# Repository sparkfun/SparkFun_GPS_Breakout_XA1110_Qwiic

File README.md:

SparkFun GPS Breakout - XA1110
========================================

[*SparkFun GPS Breakout - XA1110 (Qwiic) (SEN-14414)*](https://www.sparkfun.com/products/14414)

The Qwiic GPS uses the Titan X1 GPS module with special I2C firmware. This library talks to the GPS module over I2C.

Repository Contents
-------------------

* **/Hardware** - Eagle design files (.brd, .sch)
* **/Libraries** - Libraries for use with the SparkFun GPS Breakout
* **/Production** - Production panel files (.brd)

Documentation
--------------
* **[SparkFun I2C GPS Library](https://github.com/sparkfun/SparkFun_I2C_GPS_Arduino_Library)** - C library for the XA1110.
* **[TinyGPS library by MikalHart](https://github.com/mikalhart/TinyGPS)** - C library for the XA1110.
* **[Hookup Guide](https://learn.sparkfun.com/tutorials/sparkfun-gps-breakout---xa1110-qwiic-hookup-guide)** - Basic hookup guide for the XA1110 GPS.
* **[SparkFun Fritzing repo](https://github.com/sparkfun/Fritzing_Parts)** - Fritzing diagrams for SparkFun products.
* **[SparkFun 3D Model repo](https://github.com/sparkfun/3D_Models)** - 3D models of SparkFun products. 
* **[SparkFun Graphical Datasheets](https://github.com/sparkfun/Graphical_Datasheets)** -Graphical Datasheets for various SparkFun products.

Product Versions
----------------
* [SEN-14414](https://www.sparkfun.com/products/14414)- The Qwiic GPS uses the Titan X1 GPS module with special I2C firmware. This library talks to the GPS module over I2C.

Version History
---------------
* [v1.0.0](https://github.com/sparkfun/SparkFun_GPS_Breakout_XA1110_Qwiic/releases/tag/V_1.0.0) - Initial Release

License Information
-------------------

This product is _**open source**_! 

Please review the LICENSE.md file for license information. 

If you have any questions or concerns on licensing, please contact techsupport@sparkfun.com.

Distributed as-is; no warranty is given.

- Your friends at SparkFun.

_<COLLABORATION CREDIT>_

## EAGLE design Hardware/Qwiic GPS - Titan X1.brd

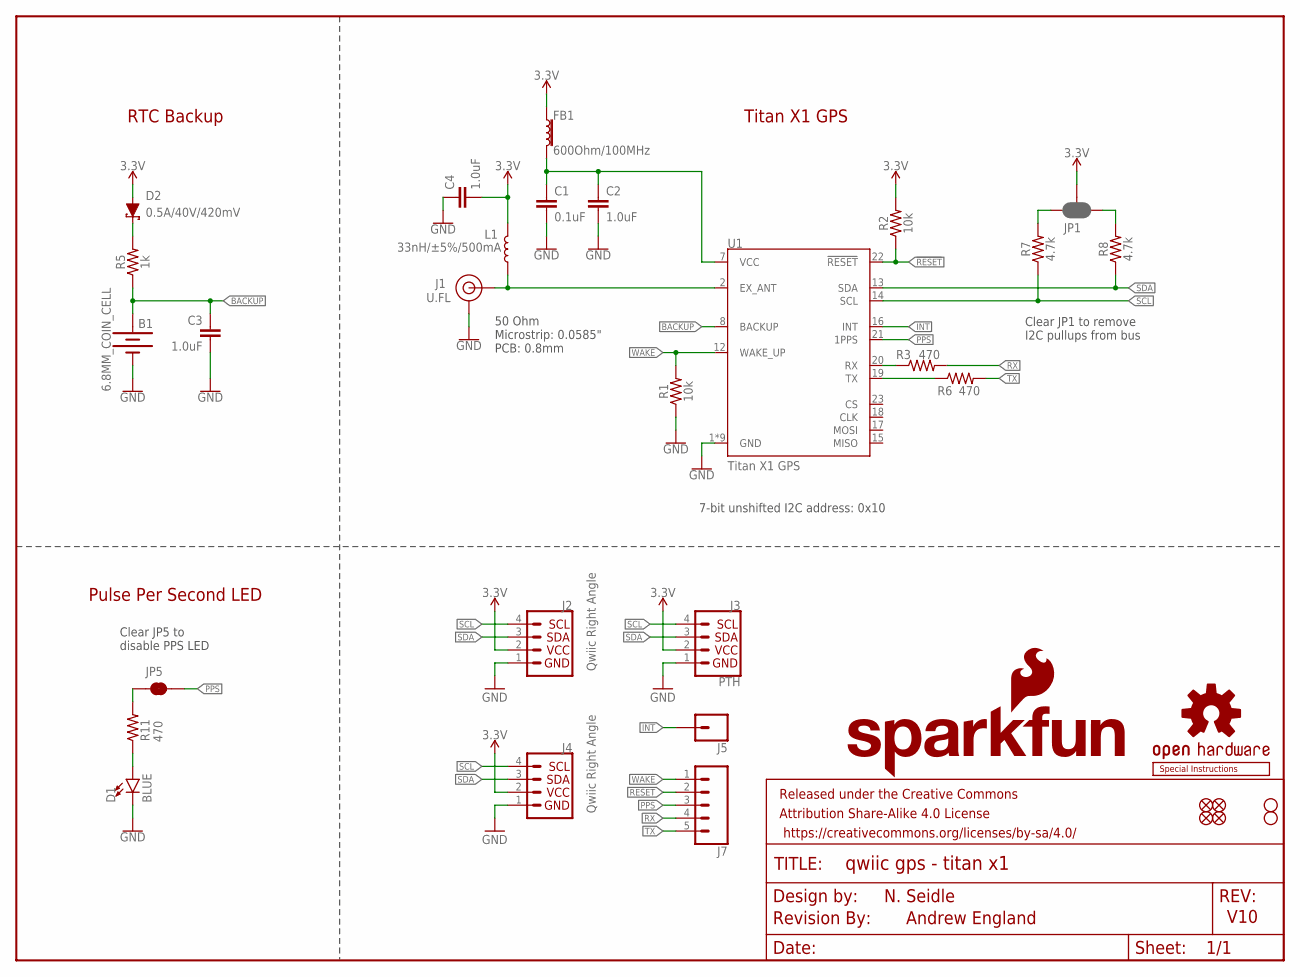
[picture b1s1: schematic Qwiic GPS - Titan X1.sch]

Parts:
B1: 6.8MM_COIN_CELL; BATTCON-6.8MM
C1: 0.1uF; 0603
C2, C3, C4: 1.0uF; 0603
D1: BLUE; LED-0603
D2: 0.5A/40V/420mV; SOD-323
FB1: 600Ohm/100MHz; 0603
FRAME1: FRAME-LETTER; CREATIVE_COMMONS
J1: U.FL
J2, J4: Qwiic Right Angle; 1X04_1MM_RA
J3: PTH; 1X04_NO_SILK
J5: CONN_01PTH_NO_SILK_YES_STOP; 1X01_NO_SILK
J7: CONN_05NO_SILK; 1X05_NO_SILK
JP1: JUMPER-SMT_3_2-NC_PASTE_SILK; SMT-JUMPER_3_2-NC_PASTE_SILK
JP2, JP6, JP7, JP8: FIDUCIALUFIDUCIAL; MICRO-FIDUCIAL
JP3, JP4: STAND-OFF
JP5: JUMPER-SMT_2_NC_TRACE_NO-SILK; SMT-JUMPER_2_NC_TRACE_NO-SILK
L1: 33nH/±5%/500mA; 0603
LOGO1: OSHW-LOGOMINI; OSHW-LOGO-MINI
LOGO2: SFE_LOGO_NAME_FLAME.1_INCH; SFE_LOGO_NAME_FLAME_.1
LOGO3: REVISION
R1, R2: 10k; 0603
R3, R6, R11: 470; 0603
R5: 1k; 0603
R7, R8: 4.7k; 0603
U1: Titan X1 GPS; TITAN_X1_GPS
U$3: SPECIAL_INSTRUCTIONS-PRODUCTION; PRODUCTION_INSTRUCTIONS

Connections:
3.3V: C4.2, D2.A, FB1.1, J2.2, J3.2 (VCC), J4.2, JP1.2, L1.2, R2.2
!RESET: J7.2, R2.1, U1.22 (!RESET)
BACKUP: B1.+, C3.1, R5.1, U1.8 (BACKUP)
EXT_ANT: J1.FEED (SIGNAL), L1.1, U1.2 (EX_ANT)
GND: B1.-, C1.2, C2.2, C3.2, C4.1, D1.C, J1.1 (GND), J1.2 (GND), J2.1, J3.1 (GND), J4.1, R1.1, U1.1 (GND), U1.3 (GND), U1.4 (GND), U1.5 (GND), U1.6 (GND), U1.9 (GND), U1.10 (GND), U1.11 (GND), U1.24 (GND)
INT: J5.1, U1.16 (INT)
unnamed: D1.A, R11.1
unnamed: JP5.1, R11.2
unnamed: JP1.1, R8.2
unnamed: D2.C, R5.2
unnamed: JP1.3, R7.2
PPS: J7.3, JP5.2, U1.21 (1PPS)
RX: J7.4, R3.2
RXLV: R3.1, U1.20 (RX)
SCL: J2.4, J3.4 (SCL), J4.4, R7.1, U1.14 (SCL)
SDA: J2.3, J3.3 (SDA), J4.3, R8.1, U1.13 (SDA)
TX: J7.5, R6.2
TXLV: R6.1, U1.19 (TX)
VCC_FILTERED: C1.1, C2.1, FB1.2, U1.7 (VCC)
WAKE: J7.1, R1.2, U1.12 (WAKE_UP)

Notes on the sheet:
N. Seidle
V10
7-bit unshifted I2C address: 0x10
Titan X1 GPS
RTC Backup
Pulse Per Second LED
50 Ohm Microstrip: 0.0585" PCB: 0.8mm
Andrew England
Clear JP1 to remove I2C pullups from bus
Clear JP5 to disable PPS LED

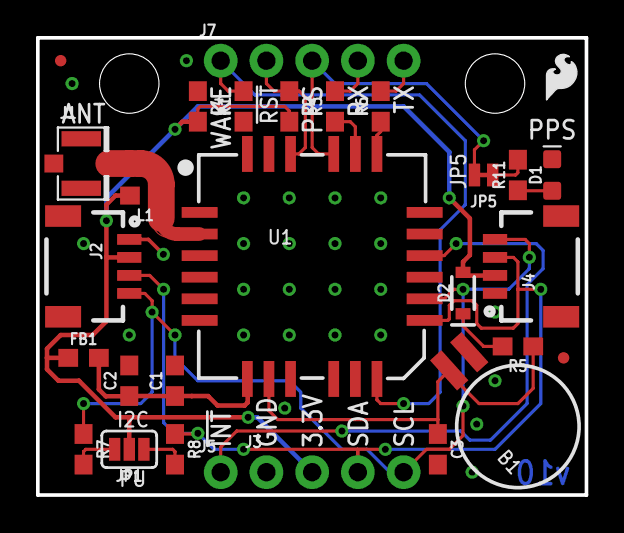
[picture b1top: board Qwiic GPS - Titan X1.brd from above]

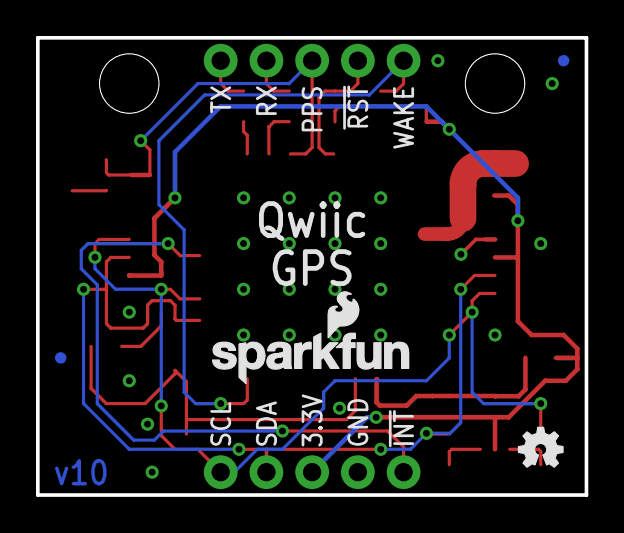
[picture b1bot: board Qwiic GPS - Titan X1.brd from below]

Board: 2 copper layers, 30.5 x 25.4 mm, 38 parts (4 on the bottom side), 20 nets.

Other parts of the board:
U$2: SFE_LOGO_FLAME_.1

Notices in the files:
parts and their libraries:
SparkFun-Resistors: Licensing: Creative Commons ShareAlike 4.0 International - https://creativecommons.org/licenses/by-sa/4.0
SparkFun-Aesthetics: Released under the Creative Commons Attribution Share-Alike 4.0 License
SparkFun-Aesthetics: https://creativecommons.org/licenses/by-sa/4.0
